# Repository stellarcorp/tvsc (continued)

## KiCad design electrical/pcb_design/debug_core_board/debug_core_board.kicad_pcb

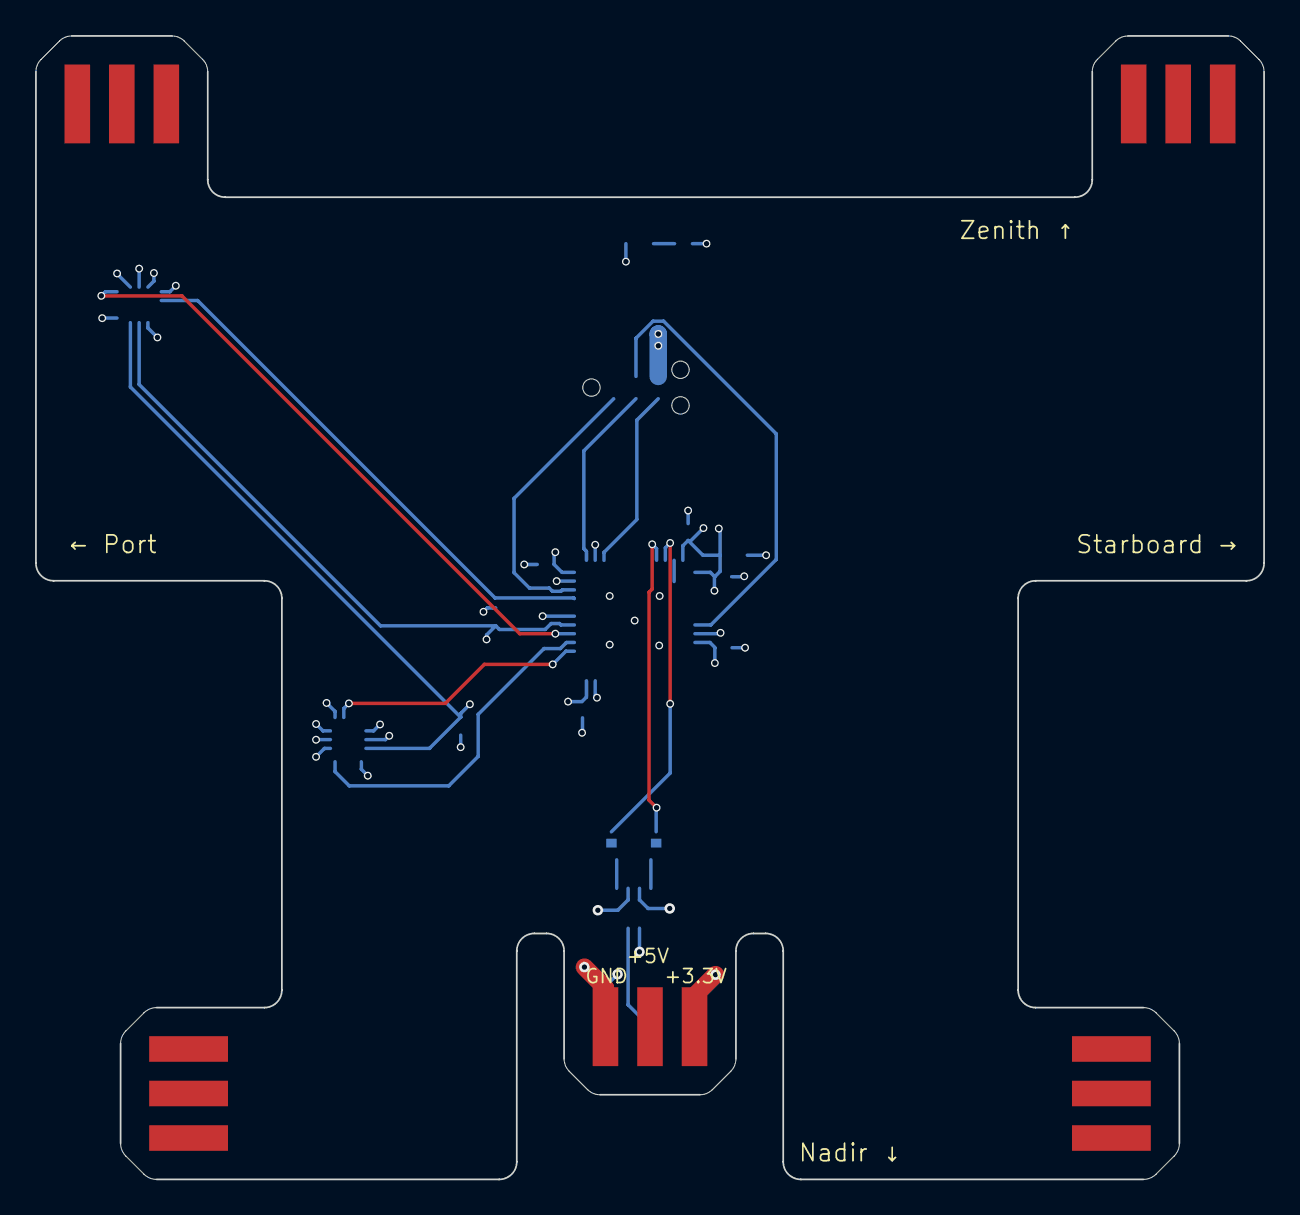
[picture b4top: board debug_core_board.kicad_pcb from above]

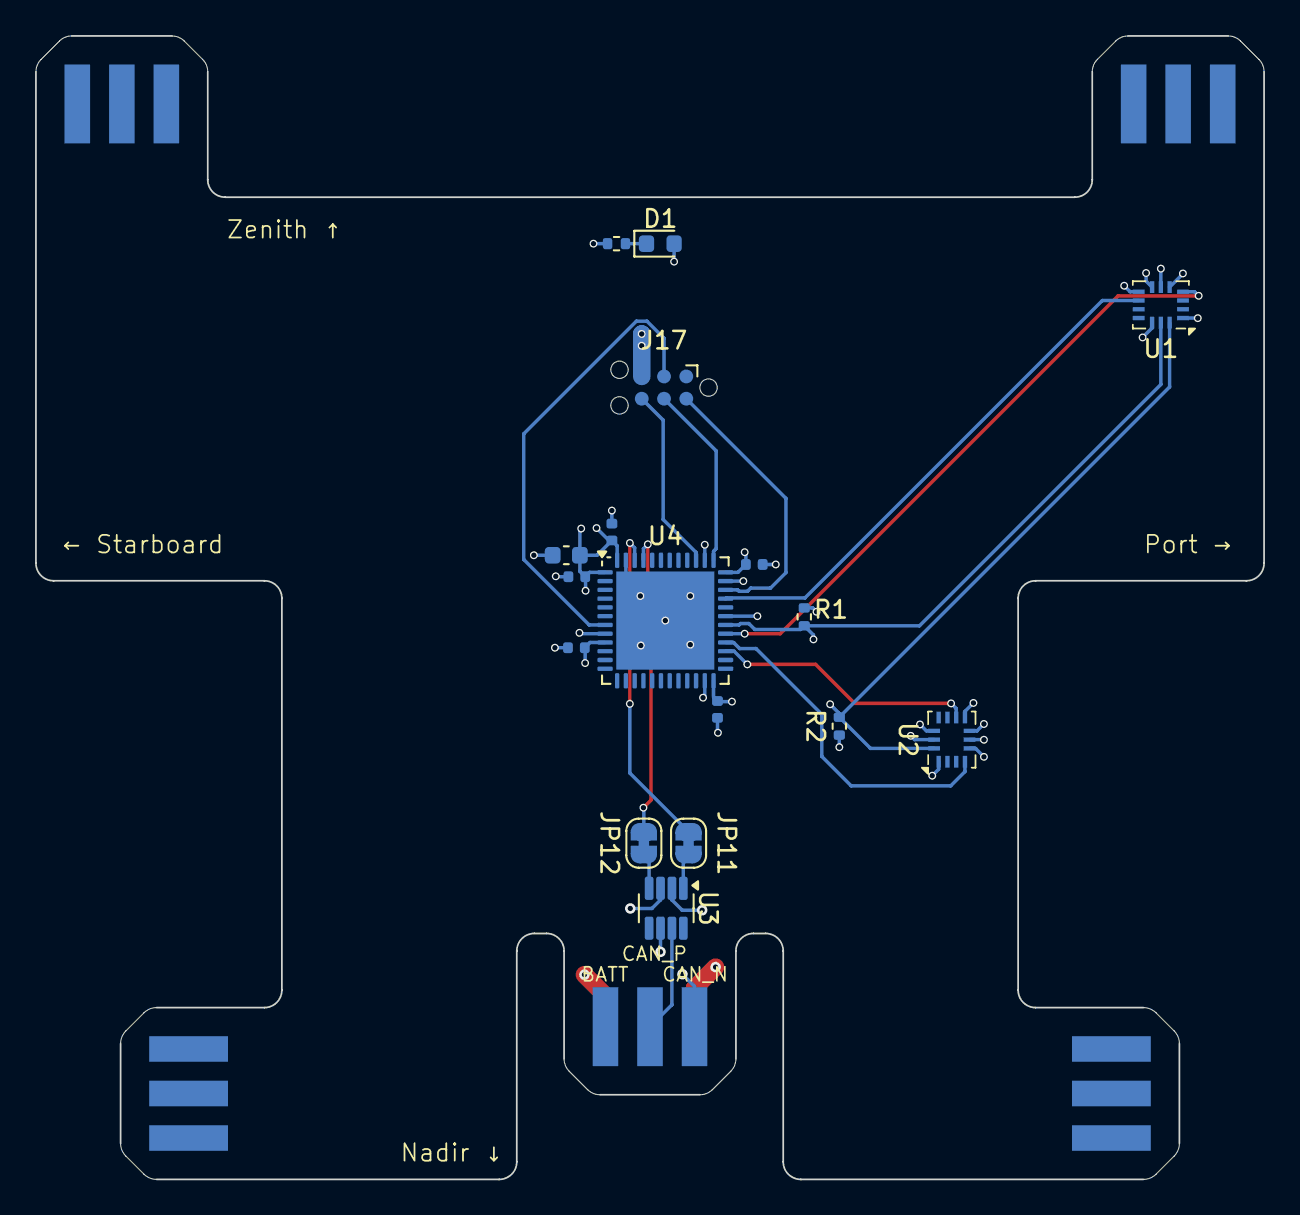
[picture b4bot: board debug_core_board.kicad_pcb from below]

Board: 4 copper layers, 70.1 x 65.2 mm, 18 parts (17 on the bottom side), 20 nets.

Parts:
C1: 10u; Nondescript_C_0603_1608Metric
C2, C3, C4, C5, C6: 100n; Nondescript_C_0402_1005Metric
D1: Blue LED; LED_0603_1608Metric
J17: STLINK_TagConnect_6; Tag-Connect_TC2030-IDC-NL_2x03_P1.27mm_Vertical
JP11, JP12: SolderJumper_2_Bridged; SolderJumper-2_P1.3mm_Bridged_RoundedPad1.0x1.5mm
PCB1: Core_Board_PCB_Shape
R1, R2: 1k5; R_0402_1005Metric
R3: 2.21k; Nondescript_R_0402_1005Metric
U1, U2: BMI323; Bosch_LGA-14_3x2.5mm_P0.5mm
U3: TCAN330; SOT-23-8
U4: STM32L452CEU6; QFN-48-1EP_7x7mm_P0.5mm_EP5.6x5.6mm

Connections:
+3.3V: C1.1, C2.1, C3.1, C4.1, C5.1, C6.1, PCB1.5 (A5), R1.1, R2.1, U1.5 (VDDIO), U1.8 (VDD), U1.12 (CSB), U2.1 (SDO), U2.5 (VDDIO), U2.8 (VDD), U2.12 (CSB), U3.3 (VCC), U4.1 (VBAT), U4.9 (VDDA), U4.24 (VDD), U4.36 (VDDUSB), U4.48 (VDD)
/MCU/DEBUG_LED_A: D1.2 (A), U4.38 (PA15)
CAN1_RX: JP12.2 (B), U4.45 (PB8)
CAN1_TX: JP11.2 (B), U4.46 (PB9)
CAN_N: PCB1.2 (A2), U3.6 (CANL)
CAN_P: PCB1.4 (A4), U3.7 (CANH)
GND: C1.2, C2.2, C3.2, C4.2, C5.2, C6.2, J17.5 (GND), PCB1.1 (A1), R3.2, U1.1 (SDO), U1.6 (GNDIO), U1.7 (GND), U2.6 (GNDIO), U2.7 (GND), U3.2 (GND), U4.8 (VSSA), U4.23 (VSS), U4.35 (VSS), U4.47 (VSS), U4.49 (VSS)
I2C1_SCL: R1.2, U1.13 (SCx), U2.13 (SCx), U4.30 (PA9)
I2C1_SDA: R2.2, U1.14 (SDx), U2.14 (SDx), U4.31 (PA10)
IMU1_INT1: U1.4 (INT1), U4.29 (PA8)
IMU1_INT2: U1.9 (INT2), U4.33 (PA12)
IMU2_INT1: U2.4 (INT1), U4.28 (PB15)
IMU2_INT2: U2.9 (INT2), U4.27 (PB14)
NRST: J17.3 (T_NRST), U4.7 (NRST)
unnamed: D1.1 (K), R3.1
unnamed: JP11.1 (A), U3.1 (TXD)
unnamed: JP12.1 (A), U3.4 (RXD)
SWCLK: J17.4 (T_SWCLK), U4.37 (PA14)
SWDIO: J17.2 (T_SWDIO), U4.34 (PA13)
TRACESWO: J17.6 (T_SWO), U4.39 (PB3)

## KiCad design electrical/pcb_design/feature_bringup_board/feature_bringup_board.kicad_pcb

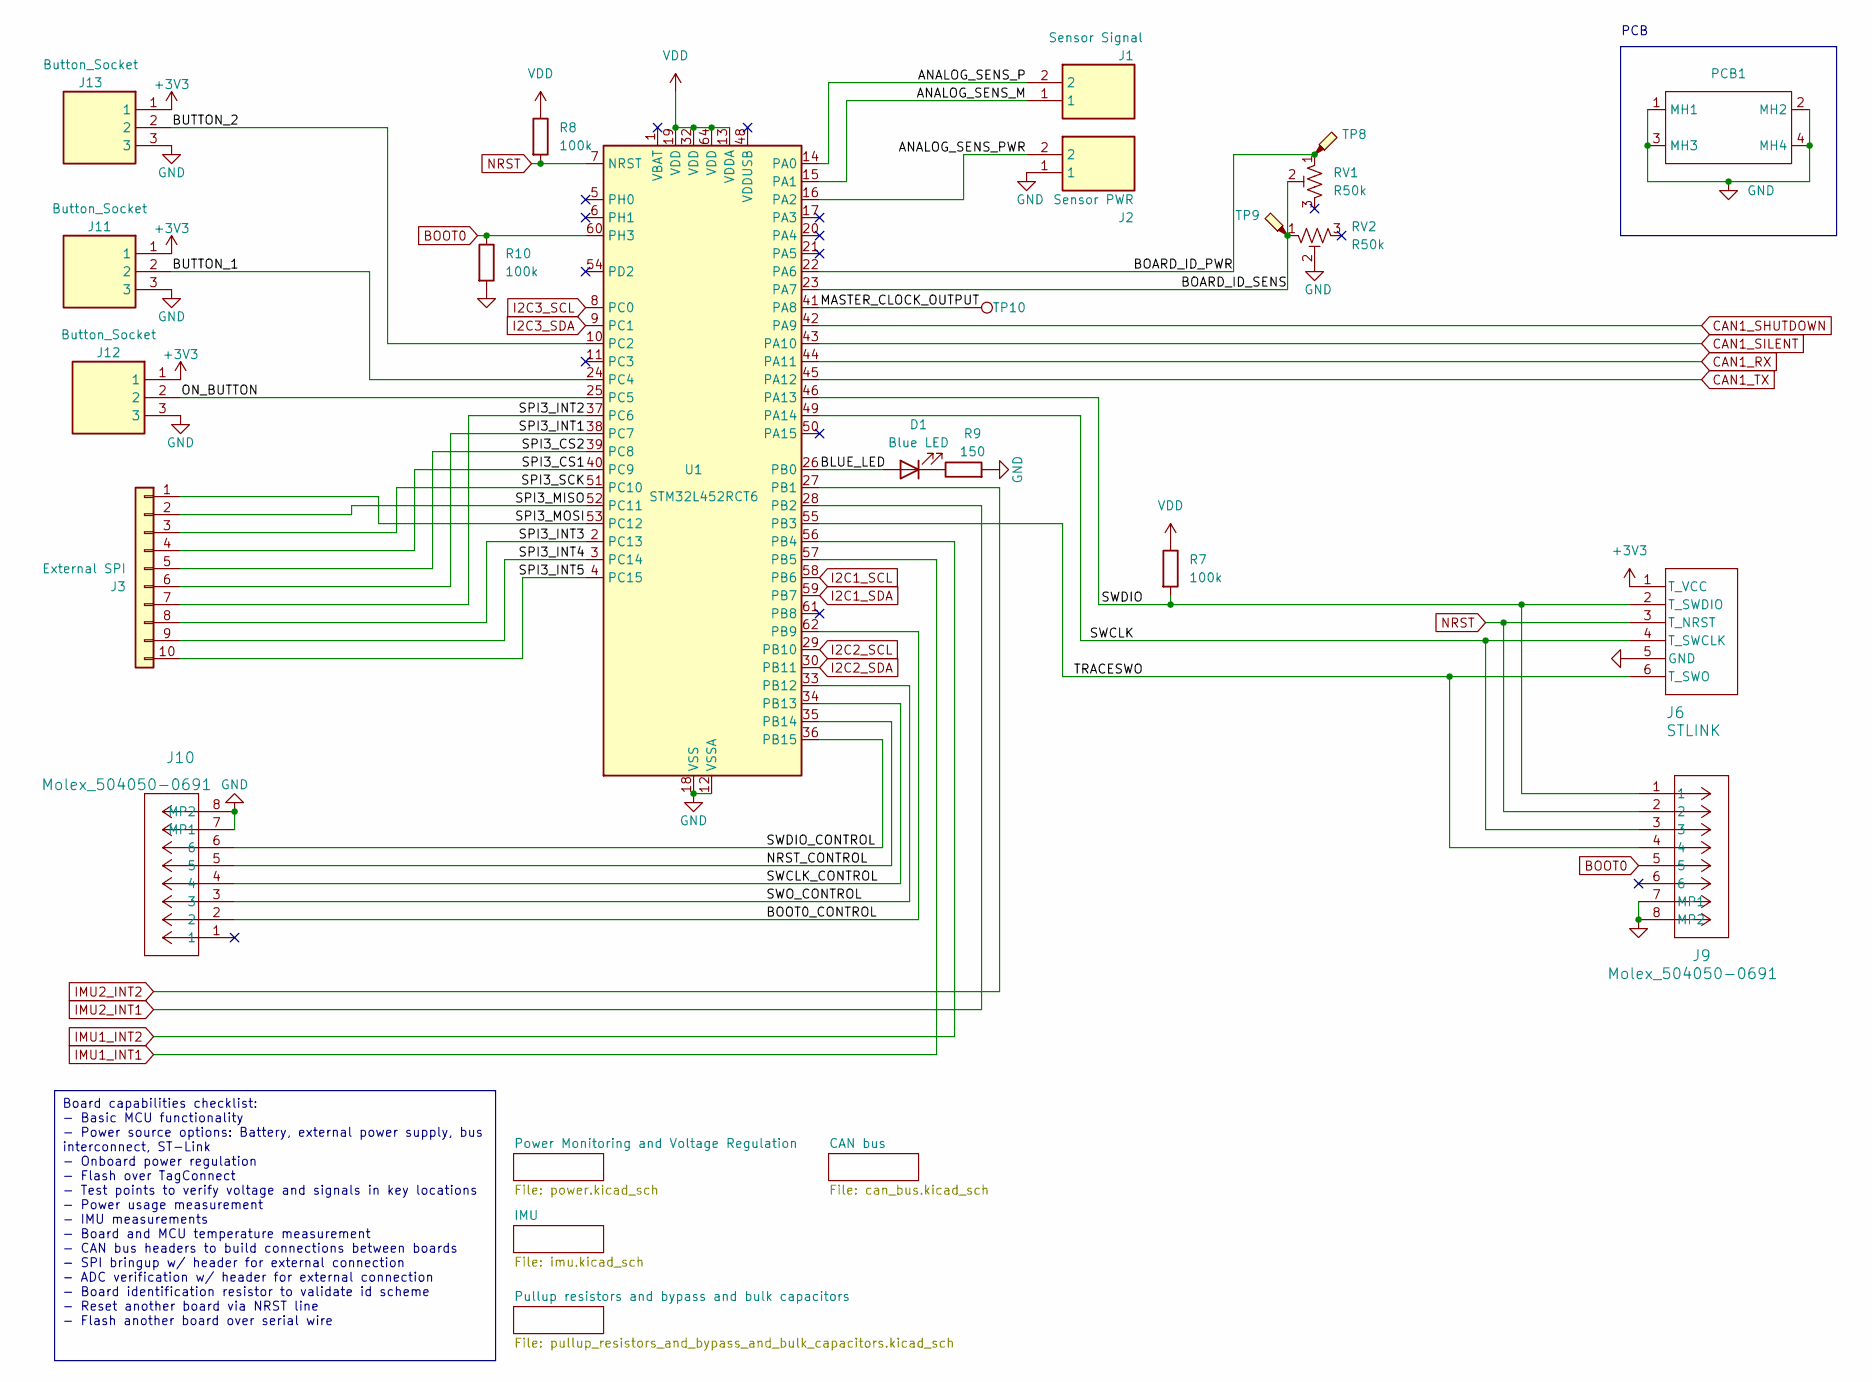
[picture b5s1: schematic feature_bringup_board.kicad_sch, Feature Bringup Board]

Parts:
D1: Blue LED; LED_0603_1608Metric; MPN C72041
J1: Sensor Signal; B2BPHKSLFSN; Manufacturer Part Number B2B-PH-K-S (LF)(SN)
J2: Sensor PWR; B2BPHKSLFSN; Manufacturer Part Number B2B-PH-K-S (LF)(SN)
J3: External SPI; PinSocket_1x10_P2.54mm_Vertical; MPN C350306
J6: STLINK; Tag-Connect_TC2030-IDC-NL_2x03_P1.27mm_Vertical; MPN NA
J9, J10: Molex_504050-0691; Manufacturer Part Number 504050-0691
J11, J12, J13: Button_Socket; SHDR3W50P0X200_1X3_790X450X600P; Manufacturer Part Number B3B-PH-K-S
PCB1: Functional_Bringup_PCB_Shape; MPN NA
R7, R8, R10: 100k; Nondescript_R_0402_1005Metric; MPN C60491
R9: 150; Nondescript_R_0402_1005Metric; MPN C138054
RV1, RV2: R50k; Potentiometer_Bourns_3314J_Vertical; MPN C50895
TP8, TP9: TestPoint_Probe; TestPoint_Pad_D2.5mm; MPN NA
TP10: TestPoint; Keystone_5002; Manufacturer Part Number 5002
U1: STM32L452RCT6; LQFP-64_10x10mm_P0.5mm; MPN C192722

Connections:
+3V3: J6.1 (T_VCC), J11.1, J12.1, J13.1; also elsewhere on the board
/ANALOG_SENS_M: J1.1, U1.15 (PA1)
/ANALOG_SENS_P: J1.2, U1.14 (PA0)
/ANALOG_SENS_PWR: J2.2, U1.16 (PA2)
/BLUE_LED: D1.2 (A), U1.26 (PB0)
/BOARD_ID_PWR: RV1.1, TP8.1, U1.22 (PA6)
/BOARD_ID_SENS: RV1.2, RV2.1, TP9.1, U1.23 (PA7)
/BOOT0_CONTROL: J10.2, U1.62 (PB9)
/BUTTON_1: J11.2, U1.24 (PC4)
/BUTTON_2: J13.2, U1.10 (PC2)
/MASTER_CLOCK_OUTPUT: TP10.1, U1.41 (PA8)
/NRST_CONTROL: J10.5, U1.35 (PB14)
/ON_BUTTON: J12.2, U1.25 (PC5)
/SPI3_CS1: J3.4, U1.40 (PC9)
/SPI3_CS2: J3.5, U1.39 (PC8)
/SPI3_INT1: J3.6, U1.38 (PC7)
/SPI3_INT2: J3.7, U1.37 (PC6)
/SPI3_INT3: J3.8, U1.2 (PC13)
/SPI3_INT4: J3.9, U1.3 (PC14)
/SPI3_INT5: J3.10, U1.4 (PC15)
/SPI3_MISO: J3.2, U1.52 (PC11)
/SPI3_MOSI: J3.1, U1.53 (PC12)
/SPI3_SCK: J3.3, U1.51 (PC10)
/SWCLK: J6.4 (T_SWCLK), J9.3, U1.49 (PA14)
/SWCLK_CONTROL: J10.4, U1.34 (PB13)
/SWDIO: J6.2 (T_SWDIO), J9.1, R7.2, U1.46 (PA13)
/SWDIO_CONTROL: J10.6, U1.36 (PB15)
/SWO_CONTROL: J10.3, U1.33 (PB12)
/TRACESWO: J6.6 (T_SWO), J9.4, U1.55 (PB3)
BOOT0: J9.5, R10.1, U1.60 (PH3)
CAN1_RX: U1.44 (PA11); also elsewhere on the board
CAN1_SHUTDOWN: U1.42 (PA9); also elsewhere on the board
CAN1_SILENT: U1.43 (PA10); also elsewhere on the board
CAN1_TX: U1.45 (PA12); also elsewhere on the board
GND: J2.1, J6.5 (GND), J9.7 (MP1), J9.8 (MP2), J10.7 (MP1), J10.8 (MP2), J11.3, J12.3, J13.3, PCB1.1 (MH1), PCB1.2 (MH2), PCB1.3 (MH3), PCB1.4 (MH4), R9.2, R10.2, RV2.2, U1.12 (VSSA), U1.18 (VSS), U1.31 (VSS), U1.47 (VSS), U1.63 (VSS); also elsewhere on the board
I2C1_SCL: U1.58 (PB6); also elsewhere on the board
I2C1_SDA: U1.59 (PB7); also elsewhere on the board
I2C2_SCL: U1.29 (PB10); also elsewhere on the board
I2C2_SDA: U1.30 (PB11); also elsewhere on the board
I2C3_SCL: U1.8 (PC0); also elsewhere on the board
I2C3_SDA: U1.9 (PC1); also elsewhere on the board
IMU1_INT1: U1.57 (PB5); also elsewhere on the board
IMU1_INT2: U1.56 (PB4); also elsewhere on the board
IMU2_INT1: U1.28 (PB2); also elsewhere on the board
IMU2_INT2: U1.27 (PB1); also elsewhere on the board
NRST: J6.3 (T_NRST), J9.2, R8.2, U1.7 (NRST)
unnamed: D1.1 (K), R9.1
VDD: R7.1, R8.1, U1.13 (VDDA), U1.19 (VDD), U1.32 (VDD), U1.64 (VDD); also elsewhere on the board

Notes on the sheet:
Board capabilities checklist: - Basic MCU functionality - Power source options: Battery, external power supply, bus interconnect, ST-Link - Onboard power regulation - Flash over TagConnect - Test points to verify voltage and signals in key locations - Power usage measurement - IMU measurements - Bo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
PCB

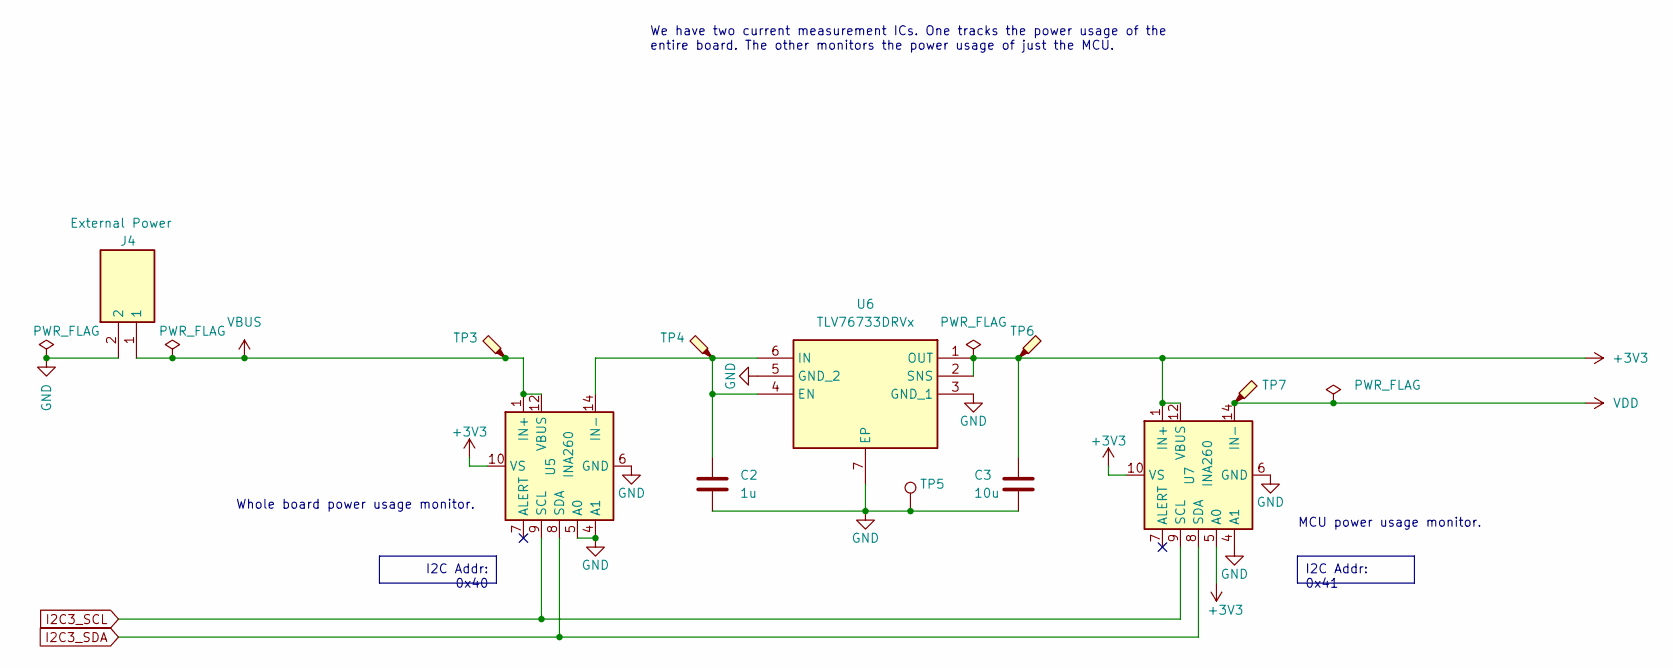
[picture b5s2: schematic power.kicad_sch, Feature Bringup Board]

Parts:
C2: 1u; Nondescript_C_0603_1608Metric; MPN C77046
C3: 10u; Nondescript_C_0603_1608Metric; MPN C344022
J4: External Power; B2BPHKSLFSN; Manufacturer Part Number B2B-PH-K-S (LF)(SN)
TP3, TP4, TP6, TP7: TestPoint_Probe; TestPoint_Pad_D2.5mm; MPN NA
TP5: TestPoint; Keystone_5001; Manufacturer Part Number 5001
U5, U7: INA260; TSSOP-16_4.4x5mm_P0.65mm; MPN C2155885
U6: TLV76733DRVx; SON65P200X200X80-7N; MPN C2867572

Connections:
+3V3: C3.1, TP6.1, U5.10 (VS), U6.1 (OUT), U6.2 (SNS), U7.1 (IN+), U7.2 (IN+), U7.3 (IN+), U7.5 (A0), U7.10 (VS), U7.12 (VBUS); also elsewhere on the board
GND: C2.2, C3.2, J4.2, TP5.1, U5.4 (A1), U5.5 (A0), U5.6 (GND), U5.11 (GND), U6.3 (GND_1), U6.5 (GND_2), U6.7 (EP), U7.4 (A1), U7.6 (GND), U7.11 (GND); also elsewhere on the board
I2C3_SCL: U5.9 (SCL), U7.9 (SCL); also elsewhere on the board
I2C3_SDA: U5.8 (SDA), U7.8 (SDA); also elsewhere on the board
unnamed: C2.1, TP4.1, U5.14 (IN-), U5.15 (IN-), U5.16 (IN-), U6.4 (EN), U6.6 (IN)
VBUS: J4.1, TP3.1, U5.1 (IN+), U5.2 (IN+), U5.3 (IN+), U5.12 (VBUS); also elsewhere on the board
VDD: TP7.1, U7.14 (IN-), U7.15 (IN-), U7.16 (IN-); also elsewhere on the board

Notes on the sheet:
I2C Addr: 0x40
I2C Addr: 0x41
MCU power usage monitor.
We have two current measurement ICs. One tracks the power usage of the entire board. The other monitors the power usage of just the MCU.
Whole board power usage monitor.

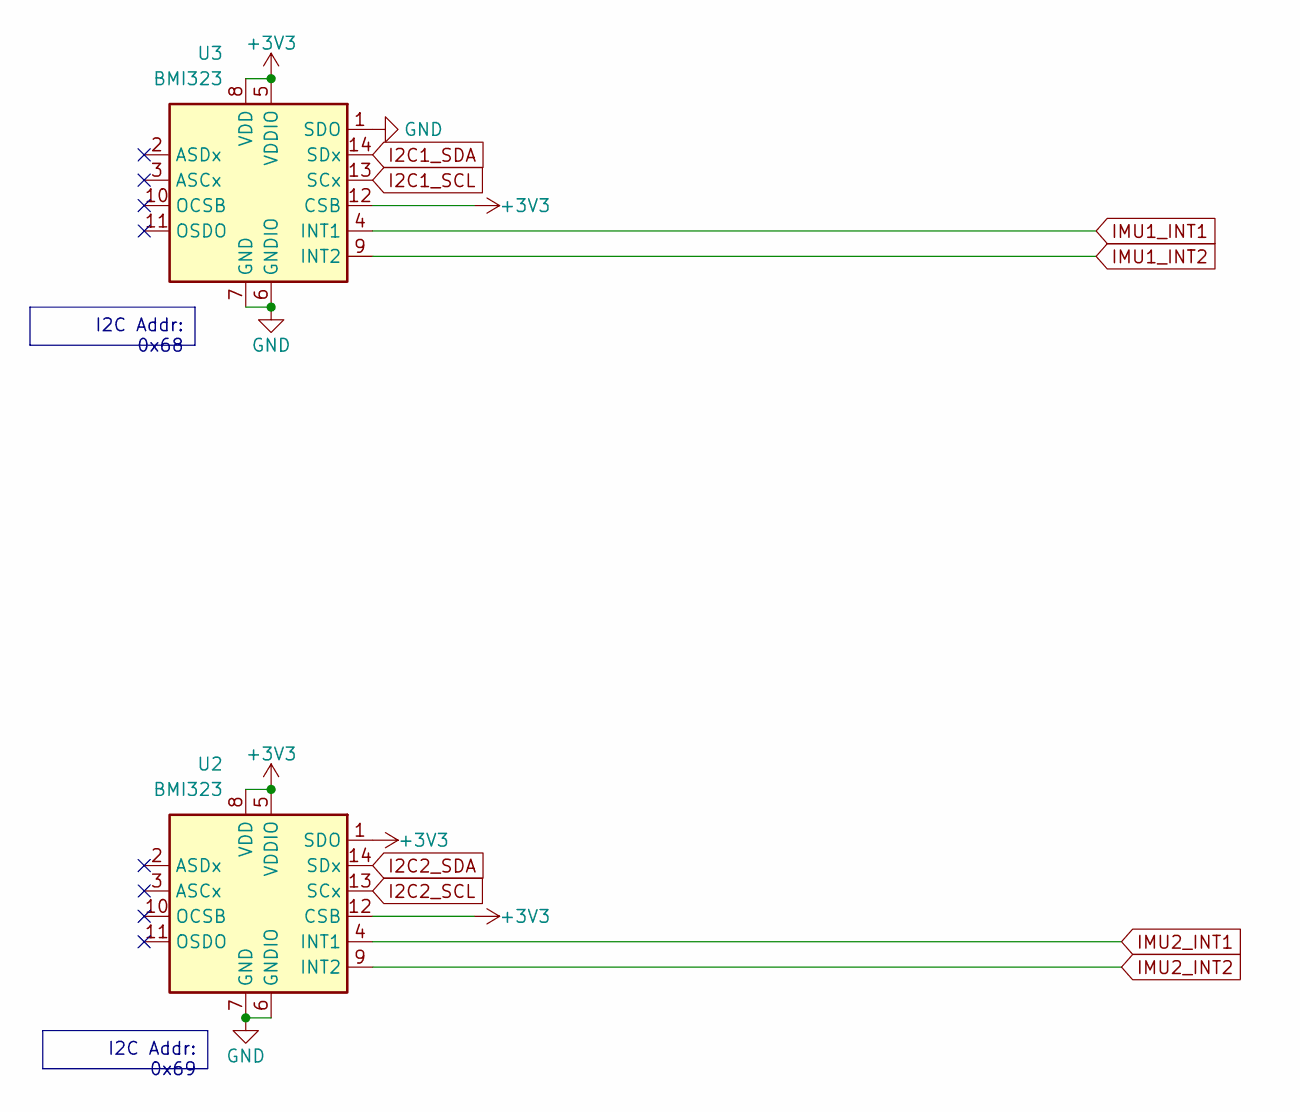
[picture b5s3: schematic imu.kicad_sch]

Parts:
U2, U3: BMI323; Bosch_LGA-14_3x2.5mm_P0.5mm; MPN C5368700

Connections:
+3V3: U2.1 (SDO), U2.5 (VDDIO), U2.8 (VDD), U2.12 (CSB), U3.5 (VDDIO), U3.8 (VDD), U3.12 (CSB); also elsewhere on the board
GND: U2.6 (GNDIO), U2.7 (GND), U3.1 (SDO), U3.6 (GNDIO), U3.7 (GND); also elsewhere on the board
I2C1_SCL: U3.13 (SCx); also elsewhere on the board
I2C1_SDA: U3.14 (SDx); also elsewhere on the board
I2C2_SCL: U2.13 (SCx); also elsewhere on the board
I2C2_SDA: U2.14 (SDx); also elsewhere on the board
IMU1_INT1: U3.4 (INT1); also elsewhere on the board
IMU1_INT2: U3.9 (INT2); also elsewhere on the board
IMU2_INT1: U2.4 (INT1); also elsewhere on the board
IMU2_INT2: U2.9 (INT2); also elsewhere on the board

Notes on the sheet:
I2C Addr: 0x69
I2C Addr: 0x68

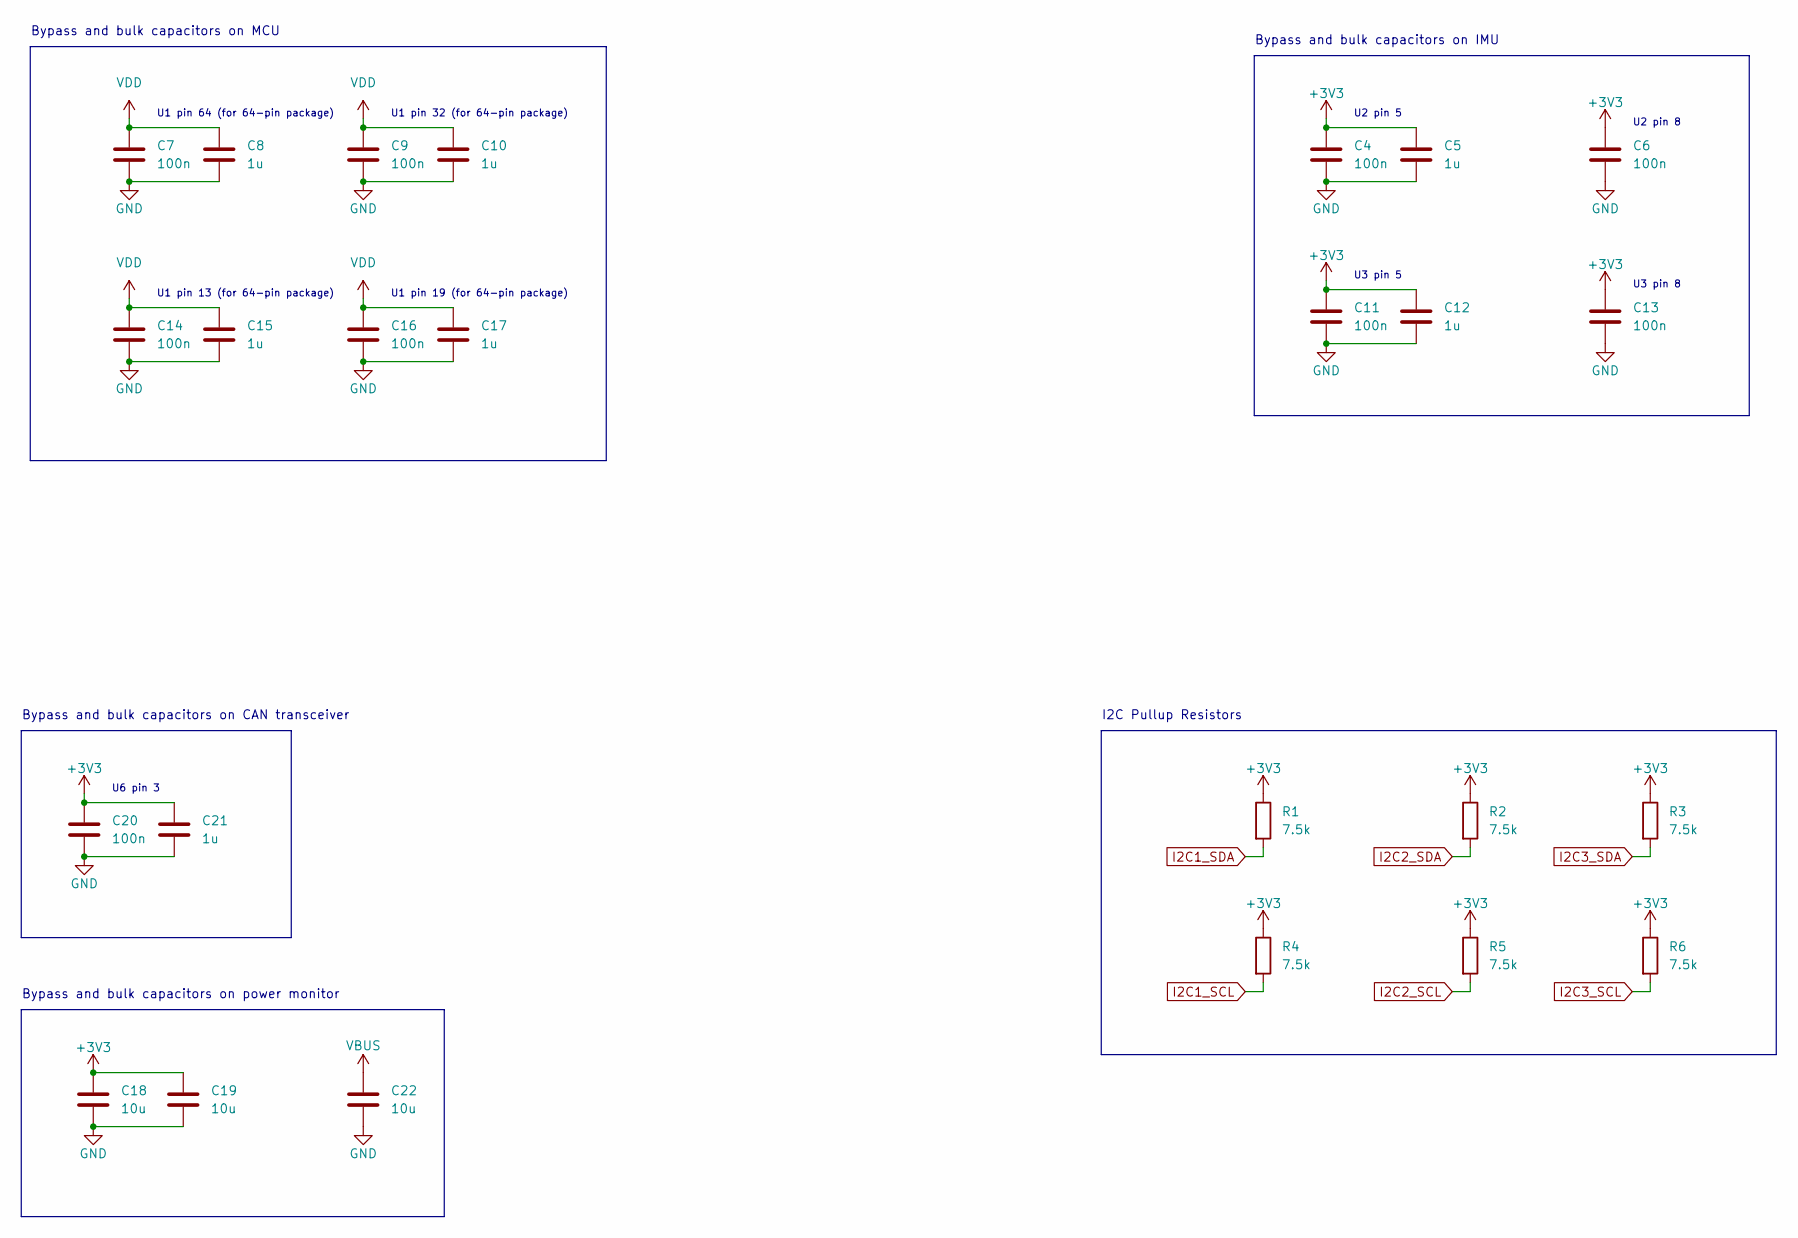
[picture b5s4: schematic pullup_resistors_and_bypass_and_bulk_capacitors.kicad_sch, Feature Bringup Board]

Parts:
C4, C6, C7, C9, C11, C13, C14, C16, C20: 100n; Nondescript_C_0402_1005Metric; MPN C77014
C5, C8, C10, C12, C15, C17, C21: 1u; Nondescript_C_0603_1608Metric; MPN C77046
C18, C19, C22: 10u; Nondescript_C_0603_1608Metric; MPN C344022
R1, R2, R3, R4, R5, R6: 7.5k; Nondescript_R_0402_1005Metric; MPN C137934

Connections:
+3V3: C4.1, C5.1, C6.1, C11.1, C12.1, C13.1, C18.1, C19.1, C20.1, C21.1, R1.1, R2.1, R3.1, R4.1, R5.1, R6.1; also elsewhere on the board
GND: C4.2, C5.2, C6.2, C7.2, C8.2, C9.2, C10.2, C11.2, C12.2, C13.2, C14.2, C15.2, C16.2, C17.2, C18.2, C19.2, C20.2, C21.2, C22.2; also elsewhere on the board
I2C1_SCL: R4.2; also elsewhere on the board
I2C1_SDA: R1.2; also elsewhere on the board
I2C2_SCL: R5.2; also elsewhere on the board
I2C2_SDA: R2.2; also elsewhere on the board
I2C3_SCL: R6.2; also elsewhere on the board
I2C3_SDA: R3.2; also elsewhere on the board
VBUS: C22.1; also elsewhere on the board
VDD: C7.1, C8.1, C9.1, C10.1, C14.1, C15.1, C16.1, C17.1; also elsewhere on the board

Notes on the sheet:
U3 pin 5
Bypass and bulk capacitors on power monitor
U1 pin 32 (for 64-pin package)
U2 pin 5
U1 pin 19 (for 64-pin package)
U6 pin 3
U1 pin 13 (for 64-pin package)
I2C Pullup Resistors
Bypass and bulk capacitors on CAN transceiver
Bypass and bulk capacitors on MCU
U1 pin 64 (for 64-pin package)
Bypass and bulk capacitors on IMU
U2 pin 8
U3 pin 8

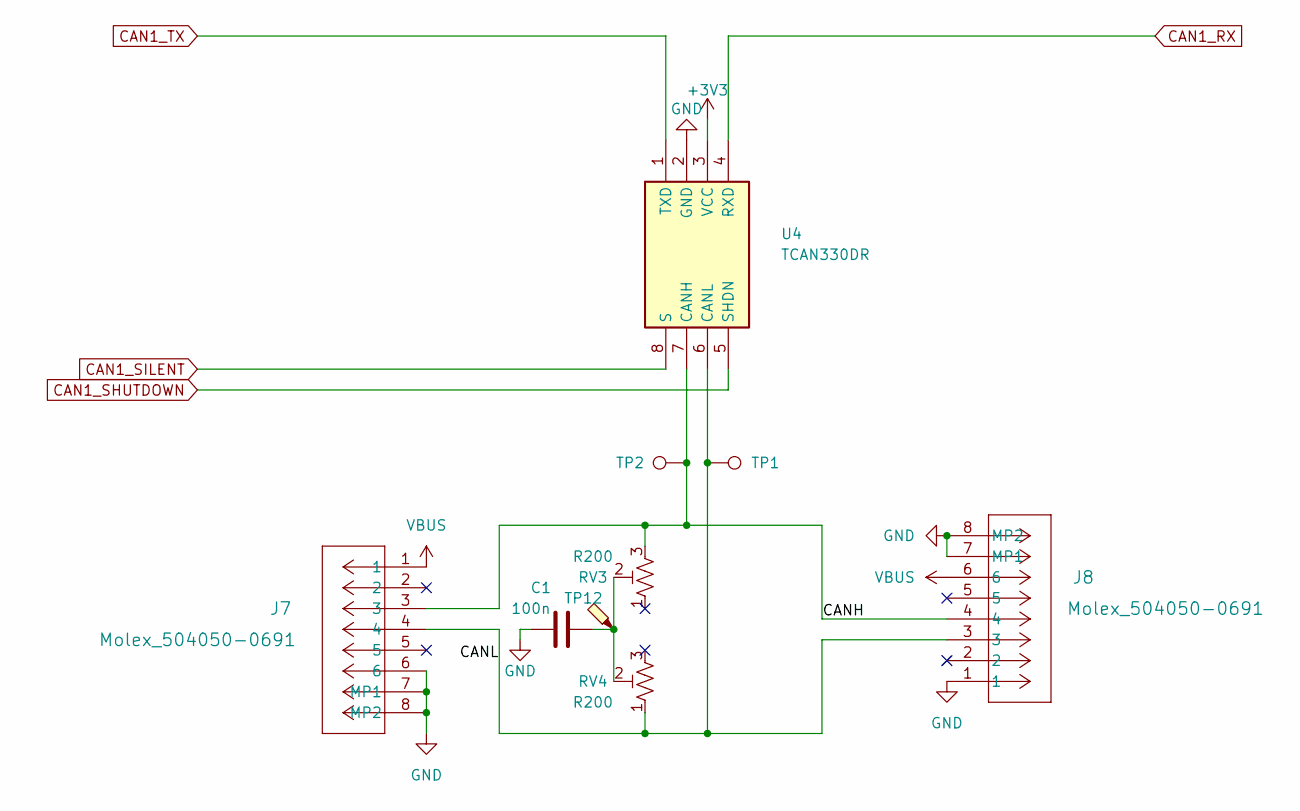
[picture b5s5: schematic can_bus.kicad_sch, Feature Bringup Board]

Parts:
C1: 100n; Nondescript_C_0402_1005Metric; MPN C77014
J7, J8: Molex_504050-0691; Manufacturer Part Number 504050-0691
RV3, RV4: R200; Potentiometer_Bourns_3314J_Vertical; MPN C124642
TP1, TP2: TestPoint; Keystone_5002; Manufacturer Part Number 5002
TP12: TestPoint_Probe; TestPoint_Pad_D2.5mm; MPN NA
U4: TCAN330DR; SOIC127P600X175-8N; Manufacturer Part Number TCAN330DR; Mouser Part Number 595-TCAN330DR

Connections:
+3V3: U4.3 (VCC); also elsewhere on the board
/CAN bus/CANH: J7.3, J8.4, RV3.3, TP2.1, U4.7 (CANH)
/CAN bus/CANL: J7.4, J8.3, RV4.1, TP1.1, U4.6 (CANL)
CAN1_RX: U4.4 (RXD); also elsewhere on the board
CAN1_SHUTDOWN: U4.5 (SHDN); also elsewhere on the board
CAN1_SILENT: U4.8 (S); also elsewhere on the board
CAN1_TX: U4.1 (TXD); also elsewhere on the board
GND: C1.1, J7.6, J7.7 (MP1), J7.8 (MP2), J8.1, J8.7 (MP1), J8.8 (MP2), U4.2 (GND); also elsewhere on the board
unnamed: C1.2, RV3.2, RV4.2, TP12.1
VBUS: J7.1, J8.6; also elsewhere on the board

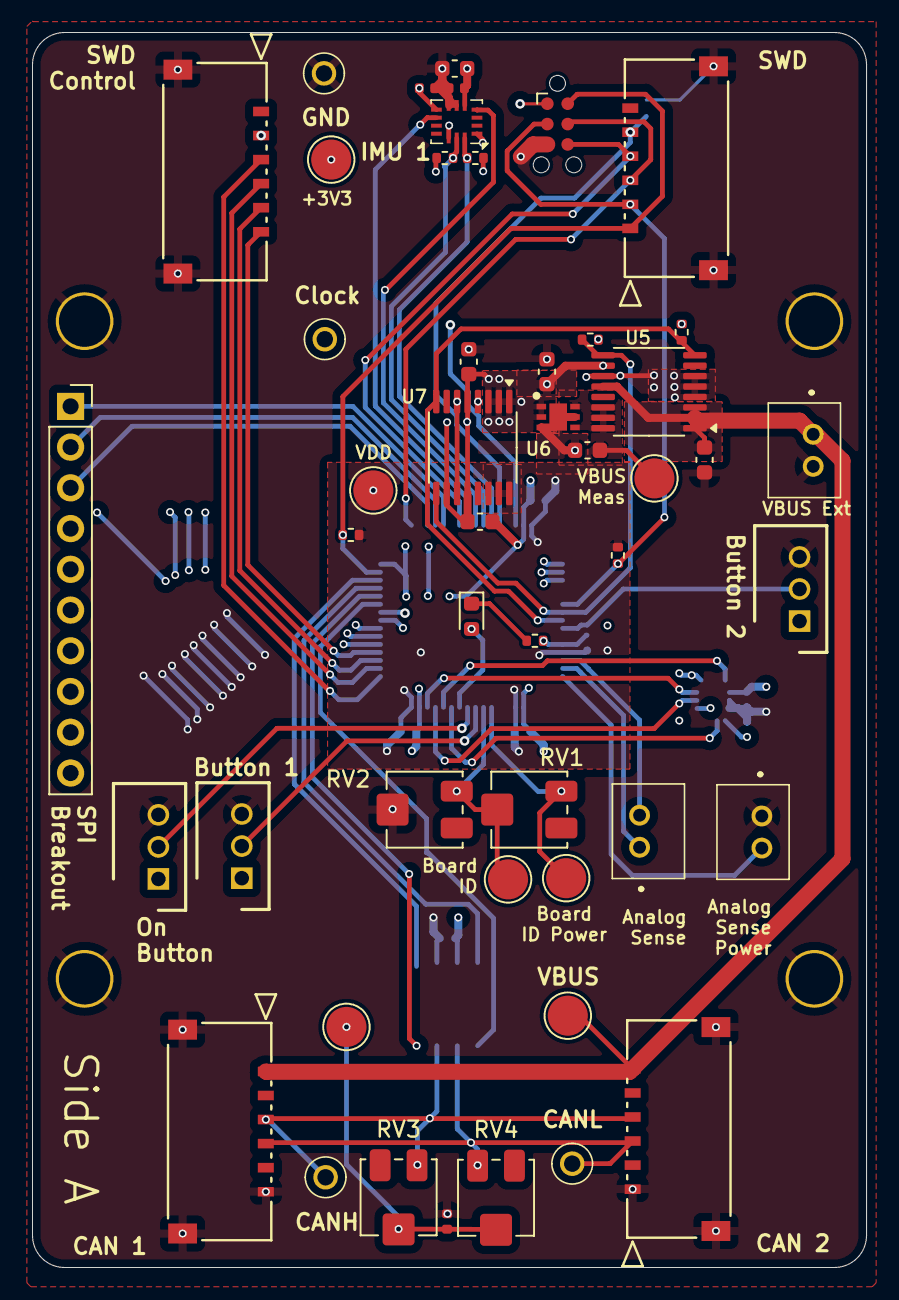
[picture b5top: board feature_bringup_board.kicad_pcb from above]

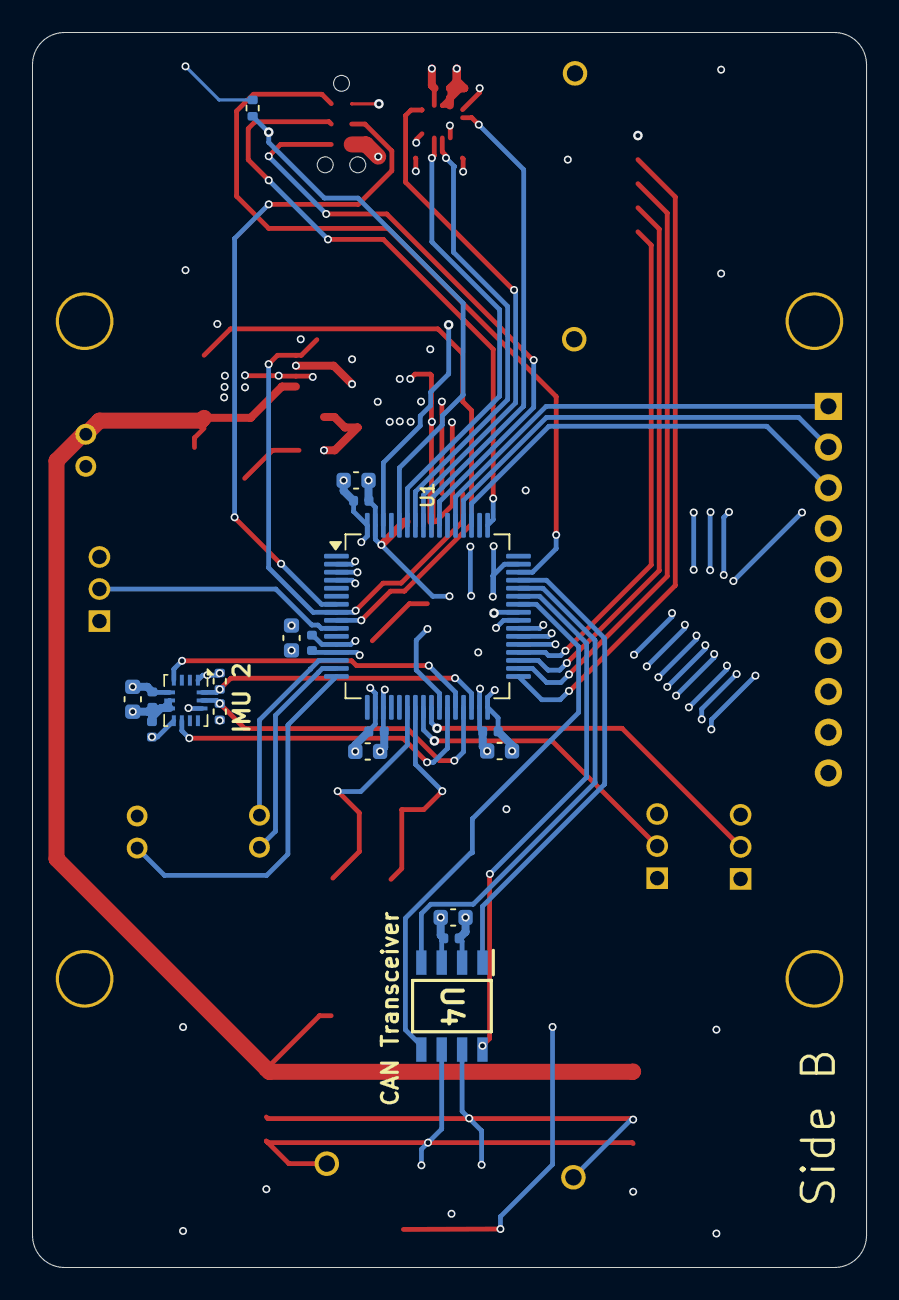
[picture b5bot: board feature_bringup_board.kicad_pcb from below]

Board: 4 copper layers, 52.0 x 77.0 mm, 68 parts (19 on the bottom side), 53 nets.

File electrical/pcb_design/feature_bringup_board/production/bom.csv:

Designator,Footprint,Quantity,Value,LCSC Part #
"C1, C11, C13, C14, C16, C20, C4, C6, C7, C9",Nondescript_C_0402_1005Metric,10,100n,C77014
"C10, C12, C15, C17, C2, C21, C5, C8",Nondescript_C_0603_1608Metric,8,1u,C77046
"C18, C19, C22, C3",Nondescript_C_0603_1608Metric,4,10u,C344022
D1,0603,1,Blue LED,C72041
J1,B2BPHKSLFSN,1,Sensor Signal,C131337
"J10, J7, J8, J9",Molex_504050-0691,4,Molex_504050-0691,C563981
"J11, J12, J13",SHDR3W50P0X200_1X3_790X450X600P,3,Button_Socket,C131339
J2,B2BPHKSLFSN,1,Sensor PWR,C131337
J3,PinSocket_1x10_P2.54mm_Vertical,1,External SPI,C350306
J4,B2BPHKSLFSN,1,External Power,C131337
"R1, R2, R3, R4, R5, R6",Nondescript_R_0402_1005Metric,6,7.5k,C137934
"R10, R7, R8",Nondescript_R_0402_1005Metric,3,100k,C60491
R9,Nondescript_R_0402_1005Metric,1,150,C138054
"RV1, RV2",Potentiometer_Bourns_3314J_Vertical,2,R50k,C50895
"RV3, RV4",Potentiometer_Bourns_3314J_Vertical,2,R200,C124642
"TP1, TP10, TP2, TP5",Keystone_5001,4,TestPoint,C238122
"TP12, TP3, TP4, TP6, TP7, TP8, TP9",TestPoint_Pad_D2.5mm,7,TestPoint_Probe,NA
U1,LQFP-64_10x10mm_P0.5mm,1,STM32L452RCT6,C192722
"U2, U3",Bosch_LGA-14_3x2.5mm_P0.5mm,2,BMI323,C5368700
U4,SOIC127P600X175-8N,1,TCAN330DR,C2652876
"U5, U7",TSSOP-16_4.4x5mm_P0.65mm,2,INA260,C2155885
U6,SON65P200X200X80-7N,1,TLV76733DRVx,C2867572

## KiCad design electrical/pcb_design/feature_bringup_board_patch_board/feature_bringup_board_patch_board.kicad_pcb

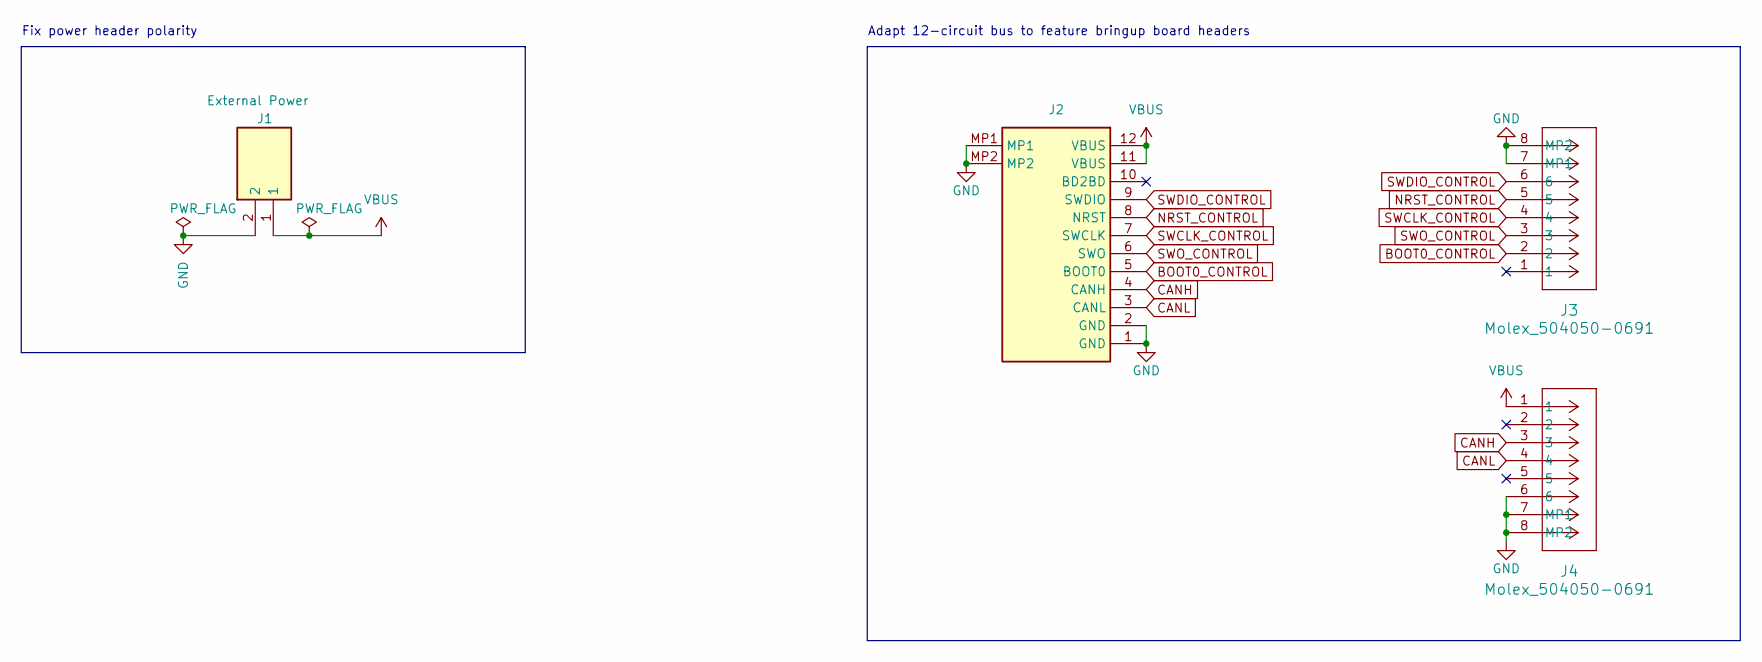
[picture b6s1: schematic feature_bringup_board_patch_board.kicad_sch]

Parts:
J1: External Power; B2BPHKSLFSN; Manufacturer Part Number B2B-PH-K-S (LF)(SN)
J2: Molex_504050-1291; Bus Connector (Target); Manufacturer Part Number 504050-1291
J3, J4: Molex_504050-0691; Manufacturer Part Number 504050-0691

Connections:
BOOT0_CONTROL: J2.5 (BOOT0), J3.2
CANH: J2.4 (CANH), J4.3
CANL: J2.3 (CANL), J4.4
GND: J1.2, J2.1 (GND), J2.2 (GND), J2.MP1, J2.MP2, J3.7 (MP1), J3.8 (MP2), J4.6, J4.7 (MP1), J4.8 (MP2)
NRST_CONTROL: J2.8 (NRST), J3.5
SWCLK_CONTROL: J2.7 (SWCLK), J3.4
SWDIO_CONTROL: J2.9 (SWDIO), J3.6
SWO_CONTROL: J2.6 (SWO), J3.3
VBUS: J1.1, J2.11 (VBUS), J2.12 (VBUS), J4.1

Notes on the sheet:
Fix power header polarity
Adapt 12-circuit bus to feature bringup board headers

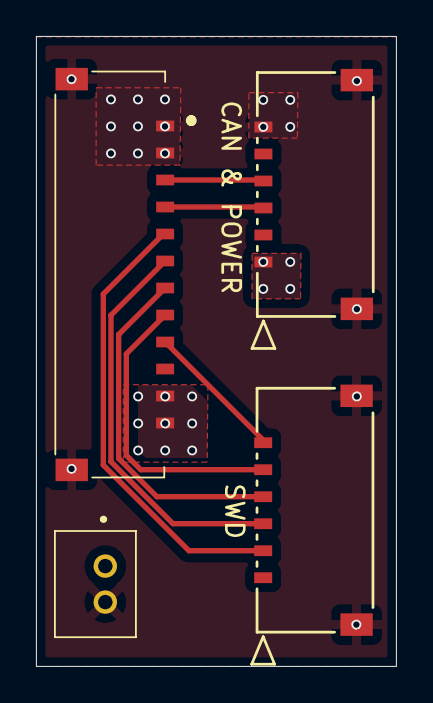
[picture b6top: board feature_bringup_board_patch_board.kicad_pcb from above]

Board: 2 copper layers, 20.0 x 35.0 mm, 4 parts (0 on the bottom side), 9 nets.

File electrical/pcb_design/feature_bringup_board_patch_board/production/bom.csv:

Designator,Footprint,Quantity,Value,LCSC Part #
J1,B2BPHKSLFSN,1,External Power,C131337
J2,Bus Connector (Target),1,Molex_504050-1291,C563982
"J3, J4",Molex_504050-0691,2,Molex_504050-0691,C563981
